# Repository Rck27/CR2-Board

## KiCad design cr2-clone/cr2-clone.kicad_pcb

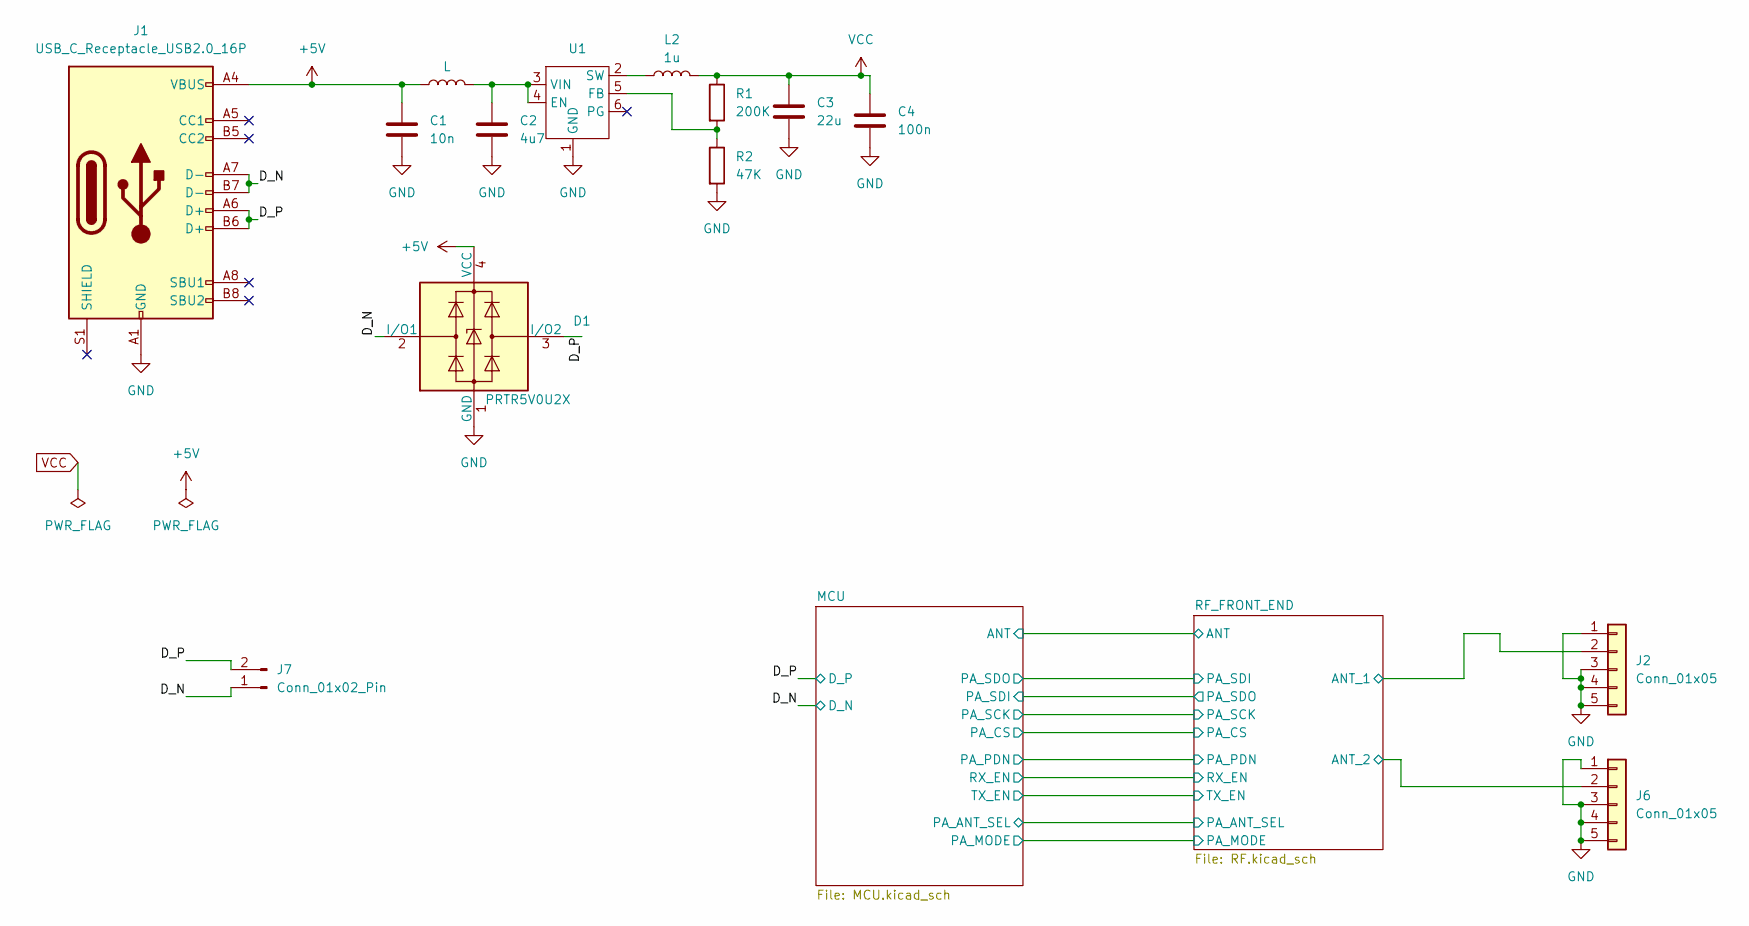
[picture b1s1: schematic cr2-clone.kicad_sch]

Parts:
C1: 10n; C_0603_1608Metric_Pad1.08x0.95mm_HandSolder
C2: 4u7; C_0603_1608Metric_Pad1.08x0.95mm_HandSolder
C3: 22u; C_0603_1608Metric_Pad1.08x0.95mm_HandSolder
C4: 100n; C_0603_1608Metric_Pad1.08x0.95mm_HandSolder
D1: PRTR5V0U2X; SOT-143
J1: USB_C_Receptacle_USB2.0_16P; USB_C_Receptacle_HCTL_HC-TYPE-C-16P-01A
J2, J6: Conn_01x05; SMA_EDGE
J7: Conn_01x02_Pin; PinSocket_1x02_P2.54mm_Vertical
L1: L; L_0603_1608Metric_Pad1.05x0.95mm_HandSolder
L2: 1u; L_0603_1608Metric_Pad1.05x0.95mm_HandSolder
R1: 200K; R_0603_1608Metric_Pad0.98x0.95mm_HandSolder
R2: 47K; R_0603_1608Metric_Pad0.98x0.95mm_HandSolder
U1: SOT-563

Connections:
+5V: C1.1, D1.4 (VCC), J1.A4 (VBUS), J1.A9 (VBUS), J1.B4 (VBUS), J1.B9 (VBUS), L1.1; also elsewhere on the board
/D_N: D1.2 (I/O1), J1.A7 (D-), J1.B7 (D-), J7.1; also elsewhere on the board
/D_P: D1.3 (I/O2), J1.A6 (D+), J1.B6 (D+), J7.2; also elsewhere on the board
/RF_FRONT_END/ANT_1: J2.2; also elsewhere on the board
/RF_FRONT_END/ANT_2: J6.2; also elsewhere on the board
GND: C1.2, C2.2, C3.2, C4.2, D1.1 (GND), J1.A1 (GND), J1.A12 (GND), J1.B1 (GND), J1.B12 (GND), J2.1, J2.3, J2.4, J2.5, J6.1, J6.3, J6.4, J6.5, R2.2, U1.1 (GND); also elsewhere on the board
unnamed: C2.1, L1.2, U1.3 (VIN), U1.4 (EN)
unnamed: R1.2, R2.1, U1.5 (FB)
unnamed: L2.1, U1.2 (SW)
VCC: C3.1, C4.1, L2.2, R1.1; also elsewhere on the board

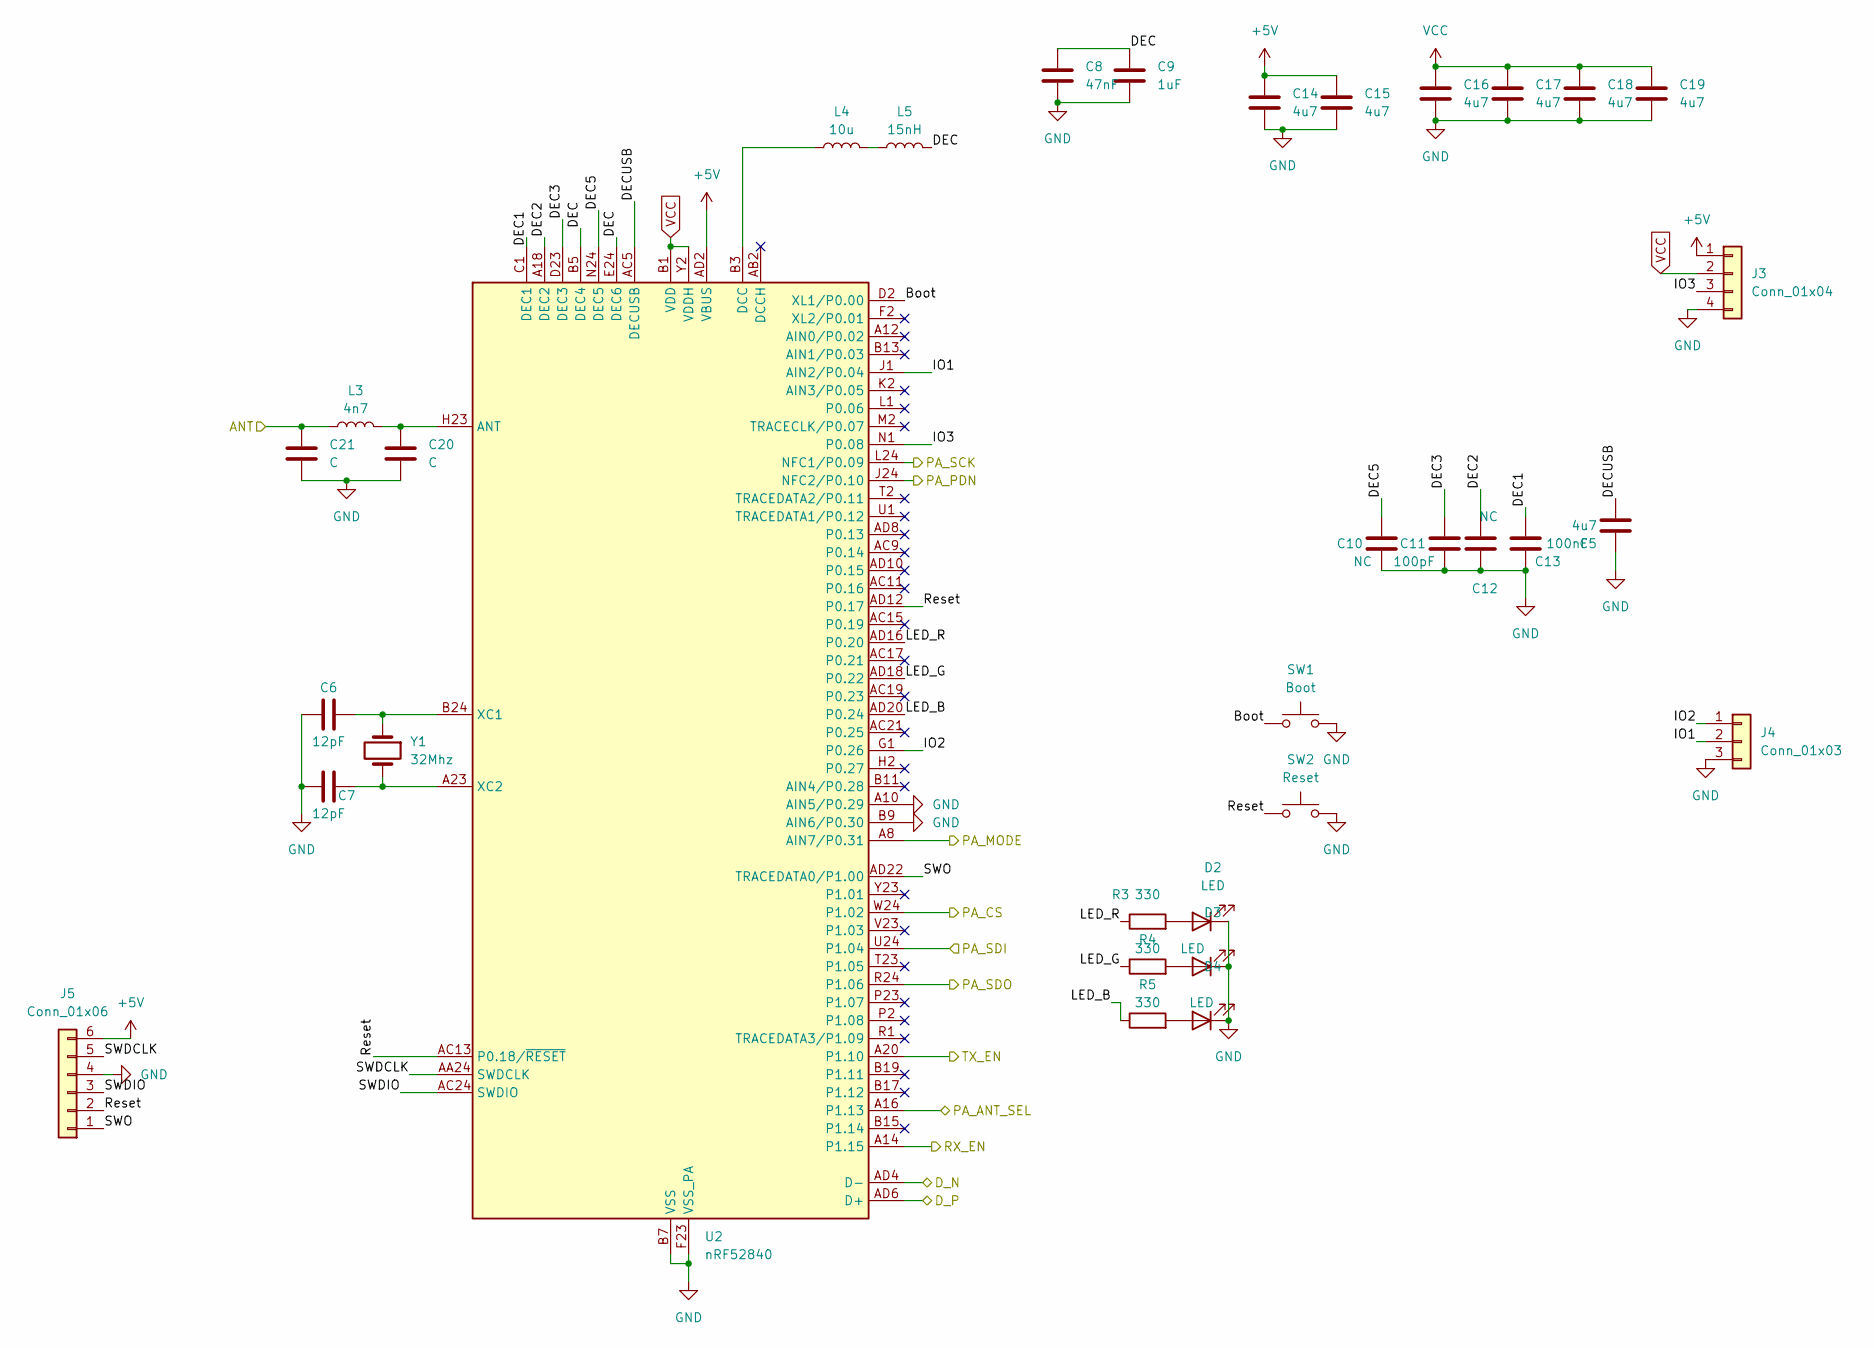
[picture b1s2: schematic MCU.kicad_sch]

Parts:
C5, C14, C15, C16, C17, C18, C19: 4u7; C_0603_1608Metric_Pad1.08x0.95mm_HandSolder
C6, C7: 12pF; C_0603_1608Metric_Pad1.08x0.95mm_HandSolder
C8: 47nF; C_0603_1608Metric_Pad1.08x0.95mm_HandSolder
C9: 1uF; C_0603_1608Metric_Pad1.08x0.95mm_HandSolder
C10, C12: NC; C_0603_1608Metric_Pad1.08x0.95mm_HandSolder
C11: 100pF; C_0603_1608Metric_Pad1.08x0.95mm_HandSolder
C13: 100nF; C_0603_1608Metric_Pad1.08x0.95mm_HandSolder
C20, C21: C; C_0603_1608Metric_Pad1.08x0.95mm_HandSolder
D2, D3, D4: LED; LED_0603_1608Metric_Pad1.05x0.95mm_HandSolder
J3: Conn_01x04; JST_EH_B4B-EH-A_1x04_P2.50mm_Vertical
J4: Conn_01x03; JST_EH_B3B-EH-A_1x03_P2.50mm_Vertical
J5: Conn_01x06; JST_EH_B6B-EH-A_1x06_P2.50mm_Vertical
L3: 4n7; L_0603_1608Metric_Pad1.05x0.95mm_HandSolder
L4: 10u; L_0603_1608Metric_Pad1.05x0.95mm_HandSolder
L5: 15nH; L_0603_1608Metric_Pad1.05x0.95mm_HandSolder
R3, R4, R5: 330; R_0603_1608Metric_Pad0.98x0.95mm_HandSolder
SW1: Boot; SW_Push_1P1T_NO_6x6mm_H9.5mm
SW2: Reset; SW_Push_1P1T_NO_6x6mm_H9.5mm
U2: nRF52840; Nordic_AQFN-73-1EP_7x7mm_P0.5mm
Y1: 32Mhz; Crystal_SMD_HC49-SD_HandSoldering

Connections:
+5V: C14.1, C15.1, J3.1, J5.6, U2.AD2 (VBUS); also elsewhere on the board
/D_N: U2.AD4 (D-); also elsewhere on the board
/D_P: U2.AD6 (D+); also elsewhere on the board
/MCU/ANT: C21.1, L3.1; also elsewhere on the board
/MCU/Boot: SW1.1, U2.D2 (XL1/P0.00)
/MCU/DEC: C8.1, C9.1, L5.2, U2.B5 (DEC4), U2.E24 (DEC6)
/MCU/DEC1: C13.2, U2.C1 (DEC1)
/MCU/DEC2: C12.2, U2.A18 (DEC2)
/MCU/DEC3: C11.2, U2.D23 (DEC3)
/MCU/DEC5: C10.2, U2.N24 (DEC5)
/MCU/DECUSB: C5.2, U2.AC5 (DECUSB)
/MCU/IO1: J4.2, U2.J1 (AIN2/P0.04)
/MCU/IO2: J4.1, U2.G1 (P0.26)
/MCU/IO3: J3.3, U2.N1 (P0.08)
/MCU/LED_B: R5.1, U2.AD20 (P0.24)
/MCU/LED_G: R4.1, U2.AD18 (P0.22)
/MCU/LED_R: R3.1, U2.AD16 (P0.20)
/MCU/PA_ANT_SEL: U2.A16 (P1.13); also elsewhere on the board
/MCU/PA_CS: U2.W24 (P1.02); also elsewhere on the board
/MCU/PA_MODE: U2.A8 (AIN7/P0.31); also elsewhere on the board
/MCU/PA_PDN: U2.J24 (NFC2/P0.10); also elsewhere on the board
/MCU/PA_SCK: U2.L24 (NFC1/P0.09); also elsewhere on the board
/MCU/PA_SDI: U2.U24 (P1.04); also elsewhere on the board
/MCU/PA_SDO: U2.R24 (P1.06); also elsewhere on the board
/MCU/RX_EN: U2.A14 (P1.15); also elsewhere on the board
/MCU/Reset: J5.2, SW2.1, U2.AC13 (P0.18/~RESET), U2.AD12 (P0.17)
/MCU/SWDCLK: J5.5, U2.AA24 (SWDCLK)
/MCU/SWDIO: J5.3, U2.AC24 (SWDIO)
/MCU/SWO: J5.1, U2.AD22 (TRACEDATA0/P1.00)
/MCU/TX_EN: U2.A20 (P1.10); also elsewhere on the board
GND: C5.1, C6.1, C7.2, C8.2, C9.2, C10.1, C11.1, C12.1, C13.1, C14.2, C15.2, C16.2, C17.2, C18.2, C19.2, C20.1, C21.2, D2.1 (K), D3.1 (K), D4.1 (K), J3.4, J4.3, J5.4, SW1.2, SW2.2, U2.A10 (AIN5/P0.29), U2.B7 (VSS), U2.B9 (AIN6/P0.30), U2.EP (VSS), U2.F23 (VSS_PA); also elsewhere on the board
unnamed: D2.2 (A), R3.2
unnamed: D3.2 (A), R4.2
unnamed: D4.2 (A), R5.2
unnamed: L4.2, L5.1
unnamed: C20.2, L3.2, U2.H23 (ANT)
unnamed: L4.1, U2.B3 (DCC)
unnamed: C6.2, U2.B24 (XC1), Y1.1
unnamed: C7.1, U2.A23 (XC2), Y1.2
VCC: C16.1, C17.1, C18.1, C19.1, J3.2, U2.A22 (VDD), U2.AD14 (VDD), U2.AD23 (VDD), U2.B1 (VDD), U2.W1 (VDD), U2.Y2 (VDDH); also elsewhere on the board

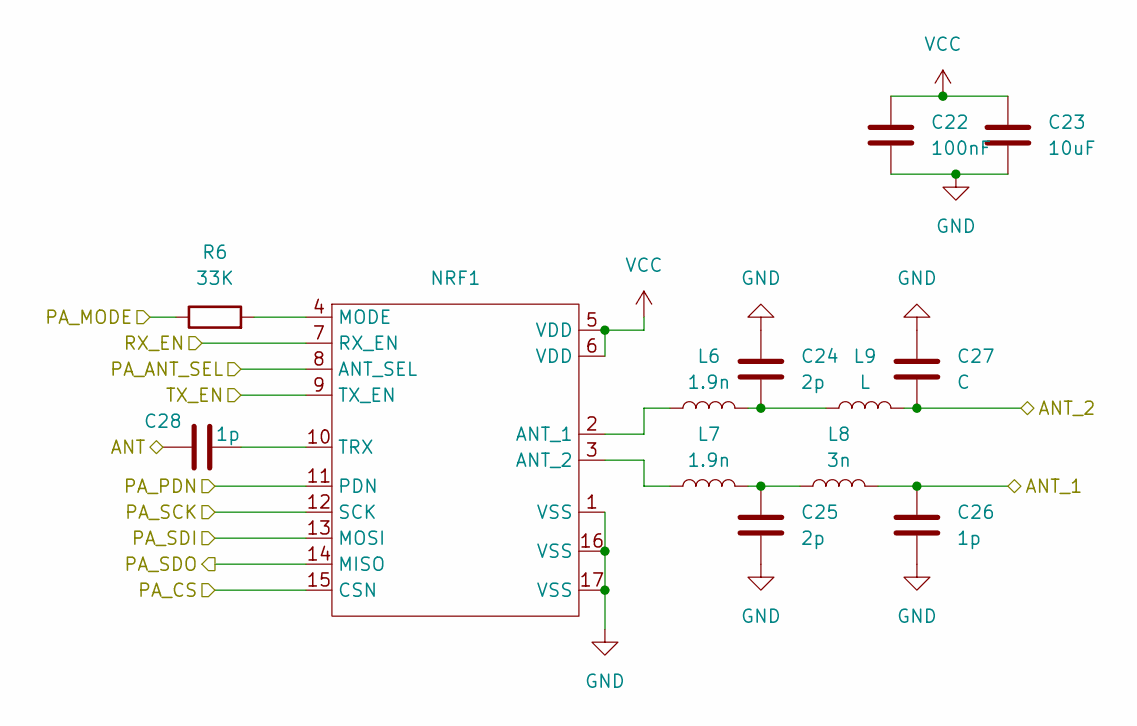
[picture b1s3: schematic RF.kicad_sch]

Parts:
C22: 100nF; C_0603_1608Metric_Pad1.08x0.95mm_HandSolder
C23: 10uF; C_0603_1608Metric_Pad1.08x0.95mm_HandSolder
C24, C25: 2p; C_0603_1608Metric_Pad1.08x0.95mm_HandSolder
C26, C28: 1p; C_0603_1608Metric_Pad1.08x0.95mm_HandSolder
C27: C; C_0603_1608Metric_Pad1.08x0.95mm_HandSolder
L6, L7: 1.9n; L_0603_1608Metric_Pad1.05x0.95mm_HandSolder
L8: 3n; L_0603_1608Metric_Pad1.05x0.95mm_HandSolder
L9: L; L_0603_1608Metric_Pad1.05x0.95mm_HandSolder
NRF1: QFN-16-1EP_4x4mm_P0.65mm_EP2.7x2.7mm_ThermalVias
R6: 33K; R_0603_1608Metric_Pad0.98x0.95mm_HandSolder

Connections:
/MCU/ANT: C28.1; also elsewhere on the board
/MCU/PA_ANT_SEL: NRF1.8 (ANT_SEL); also elsewhere on the board
/MCU/PA_CS: NRF1.15 (CSN); also elsewhere on the board
/MCU/PA_MODE: R6.1; also elsewhere on the board
/MCU/PA_PDN: NRF1.11 (PDN); also elsewhere on the board
/MCU/PA_SCK: NRF1.12 (SCK); also elsewhere on the board
/MCU/PA_SDI: NRF1.14 (MISO); also elsewhere on the board
/MCU/PA_SDO: NRF1.13 (MOSI); also elsewhere on the board
/MCU/RX_EN: NRF1.7 (RX_EN); also elsewhere on the board
/MCU/TX_EN: NRF1.9 (TX_EN); also elsewhere on the board
/RF_FRONT_END/ANT_1: C26.1, L8.2; also elsewhere on the board
/RF_FRONT_END/ANT_2: C27.2, L9.2; also elsewhere on the board
GND: C22.2, C23.2, C24.1, C25.2, C26.2, C27.1, NRF1.1 (VSS), NRF1.16 (VSS), NRF1.17 (VSS); also elsewhere on the board
unnamed: C24.2, L6.2, L9.1
unnamed: C25.1, L7.2, L8.1
unnamed: L6.1, NRF1.2 (ANT_1)
unnamed: L7.1, NRF1.3 (ANT_2)
unnamed: NRF1.4 (MODE), R6.2
unnamed: C28.2, NRF1.10 (TRX)
VCC: C22.1, C23.1, NRF1.5 (VDD), NRF1.6 (VDD); also elsewhere on the board

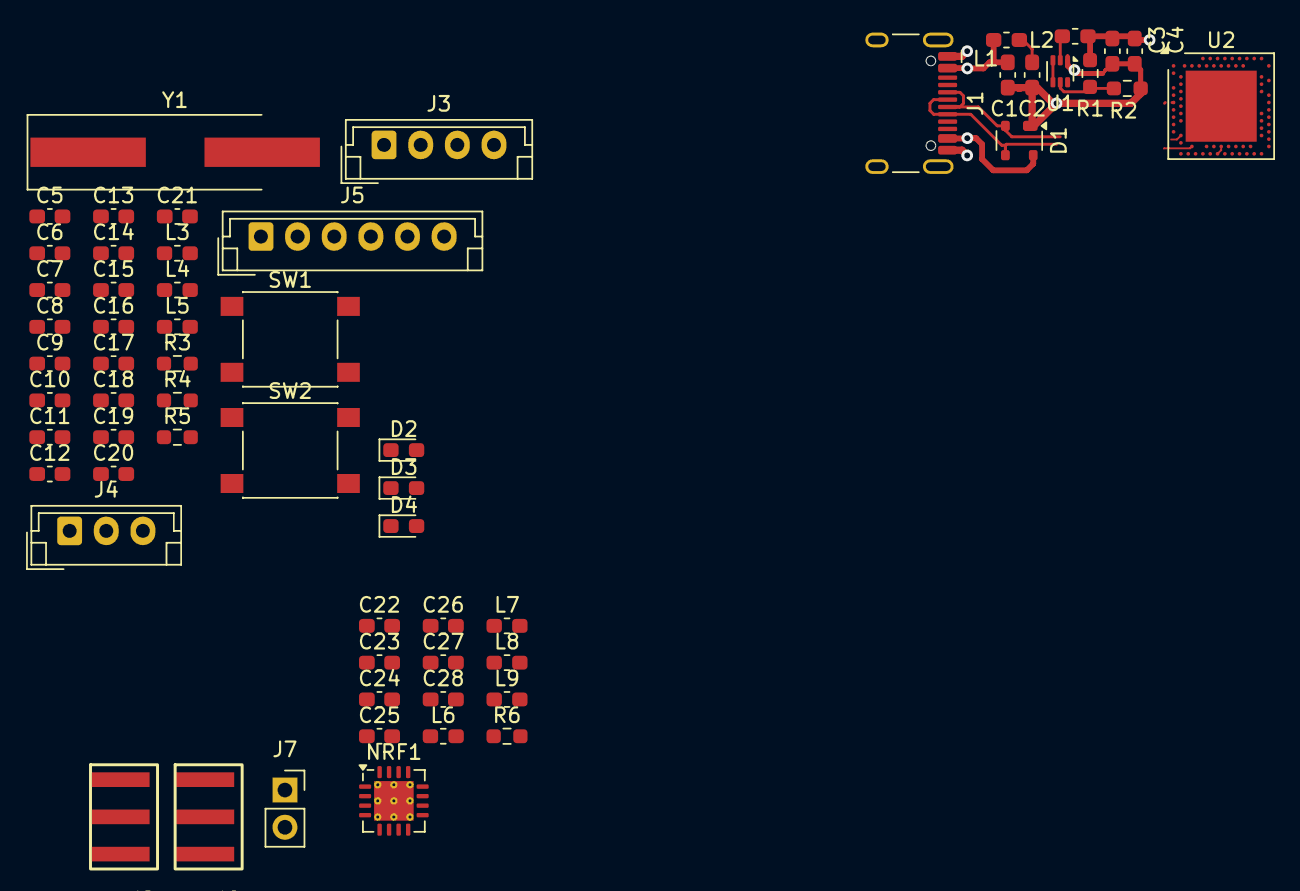
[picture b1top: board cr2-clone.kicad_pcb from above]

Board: 4 copper layers, 60 parts (0 on the bottom side), 51 nets.

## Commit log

2026-01-22 added power block
2026-01-31 added peripherals
2026-02-04 added footprint, init pcb design
2026-02-05 started component placing
